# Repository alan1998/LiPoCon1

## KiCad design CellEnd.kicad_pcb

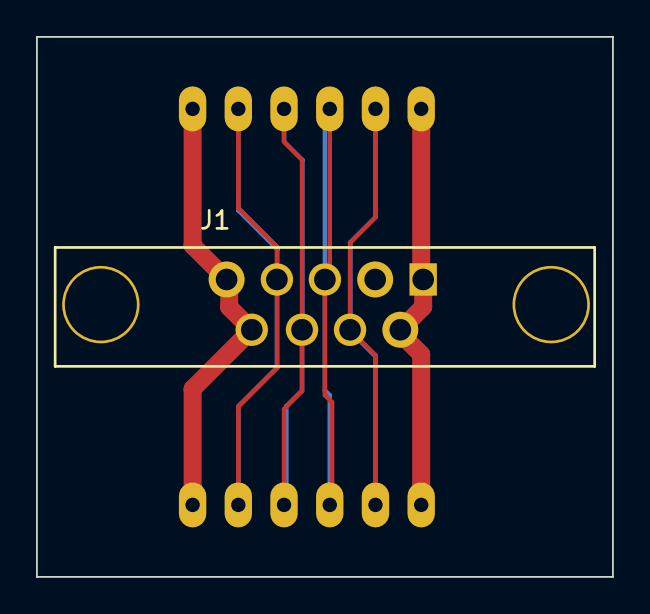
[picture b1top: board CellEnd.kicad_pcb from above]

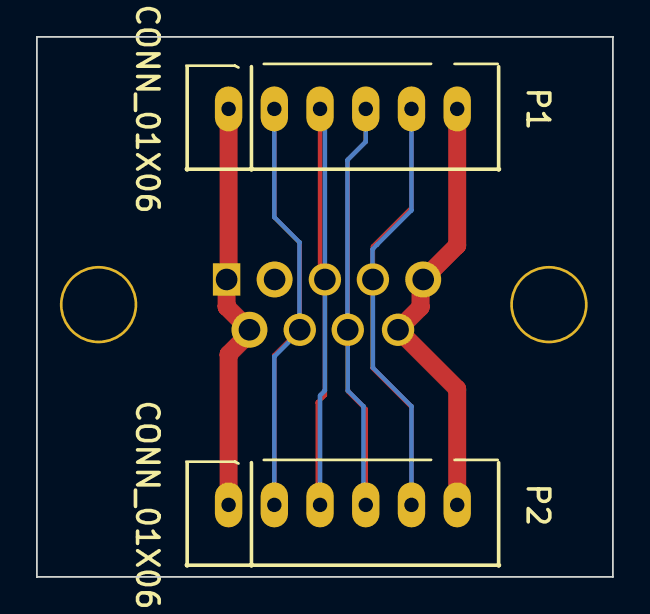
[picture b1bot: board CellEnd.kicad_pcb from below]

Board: 2 copper layers, 32.0 x 30.0 mm, 3 parts (2 on the bottom side), 6 nets.

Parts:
J1: DB9; DB9FD
P1, P2: CONN_01X06; JST-XH6

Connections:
/1s: J1.4, P1.5, P2.5
/2s: J1.8, P1.4, P2.4
/3s: J1.3, P1.3, P2.3
/4s: J1.7, P1.2, P2.2
/5s: J1.1, J1.6, P1.1, P2.1
/Gnd: J1.5, J1.9, P1.6, P2.6

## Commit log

2015-04-27 LiPo 5S charge balance connector to 9pin D
